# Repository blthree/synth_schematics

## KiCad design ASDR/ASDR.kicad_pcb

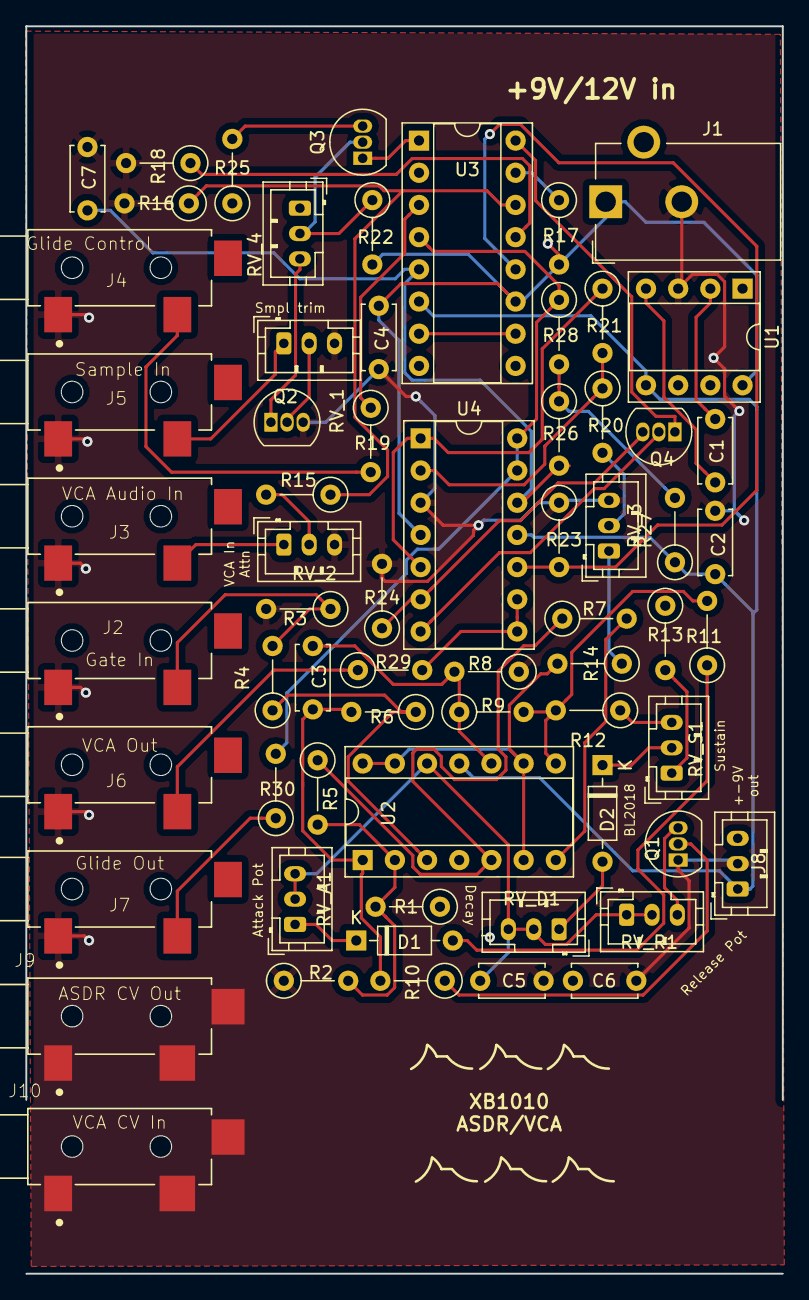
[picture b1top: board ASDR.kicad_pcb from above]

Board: 2 copper layers, 59.7 x 98.4 mm, 65 parts (0 on the bottom side), 52 nets.

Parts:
C1, C2, C5: 10uF; C_Disc_D5.0mm_W2.5mm_P5.00mm
C3: 10nF; C_Disc_D5.0mm_W2.5mm_P5.00mm
C4, C6: 100nF; C_Disc_D5.0mm_W2.5mm_P5.00mm
C7: 1uF; C_Disc_D5.0mm_W2.5mm_P5.00mm
D1, D2: D; D_DO-35_SOD27_P7.62mm_Horizontal
J1: Jack-DC; BarrelJack_CUI_PJ-102AH_Horizontal
J2: Gate In; CUI_SJ2-3592B-SMT-TR
J3: VCA Audio In; CUI_SJ2-3592B-SMT-TR
J4: Glide Control; CUI_SJ2-3592B-SMT-TR
J5: Sample In; CUI_SJ2-3592B-SMT-TR
J6: VCA Out; CUI_SJ2-3592B-SMT-TR
J7: Glide Out; CUI_SJ2-3592B-SMT-TR
J8: Power Out; JST_PH_B3B-PH-K_1x03_P2.00mm_Vertical
J9: ASDR CV Out; CUI_SJ2-3592B-SMT-TR
J10: VCA CV In; CUI_SJ2-3592B-SMT-TR
Q1, Q3, Q4: BC559; TO-92_Inline
Q2: BC548; TO-92_Inline
R1, R10, R20, R21, R22, R25: 33K; R_Axial_DIN0207_L6.3mm_D2.5mm_P5.08mm_Vertical
R2, R4, R11, R14, R16, R18, R29, R30: 1K; R_Axial_DIN0207_L6.3mm_D2.5mm_P5.08mm_Vertical
R3: 22K; R_Axial_DIN0207_L6.3mm_D2.5mm_P5.08mm_Vertical
R5, R12, R13, R15, R17, R23: 10K; R_Axial_DIN0207_L6.3mm_D2.5mm_P5.08mm_Vertical
R6, R7, R8, R9, R26, R27, R28: 1M; R_Axial_DIN0207_L6.3mm_D2.5mm_P5.08mm_Vertical
R19: 100K; R_Axial_DIN0207_L6.3mm_D2.5mm_P5.08mm_Vertical
R24: 5K; R_Axial_DIN0207_L6.3mm_D2.5mm_P5.08mm_Vertical
RV_1, RV_2, RV_3, RV_4: 100K; JST_PH_B3B-PH-K_1x03_P2.00mm_Vertical
RV_A1: 1M; JST_PH_B3B-PH-K_1x03_P2.00mm_Vertical
RV_D1: 1M; JST_PH_B3B-PH-K_1x03_P2.00mm_Vertical
RV_R1: 1M; JST_PH_B3B-PH-K_1x03_P2.00mm_Vertical
RV_S1: 10K; JST_PH_B3B-PH-K_1x03_P2.00mm_Vertical
U1: LTC1044; DIP-8_W7.62mm_Socket
U2, U4: LM324; DIP-14_W7.62mm_Socket
U3: LM13700; DIP-16_W7.62mm_Socket

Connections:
+9V: C4.2, C6.2, J1.1, J8.3, R1.1, R13.1, R17.2, R22.2, R25.1, RV_4.1, U1.8, U2.4, U3.11, U4.4
-9V: C2.2, J8.1, R27.1, U1.5, U2.11, U3.6, U4.11
GND: C2.1, C4.1, C5.2, C6.1, C7.1, J1.2, J2.S, J3.S, J4.S, J5.S, J6.S, J7.S, J8.2, J9.S, J10.S, Q1.1, Q2.3, R2.1, R3.2, R8.1, R16.2, R18.2, R23.1, R24.2, RV_1.3, RV_2.3, RV_3.3, U1.3, U4.3
unnamed: C1.1, U1.2
unnamed: C1.2, U1.4
unnamed: C3.1, R8.2, R9.1, U2.10
unnamed: C3.2, R6.2, R10.2, U2.1
unnamed: C5.1, RV_A1.2, RV_A1.3, RV_D1.2, RV_D1.3, RV_R1.1, RV_R1.2, U2.12
unnamed: C7.2, R26.2, U3.5, U4.12
unnamed: D1.1, RV_A1.1
unnamed: D1.2, R11.1
unnamed: D2.1, RV_S1.2
unnamed: D2.2, RV_D1.1
unnamed: J2.T, R3.1, R4.2
unnamed: J3.T, RV_2.1
unnamed: J4.T, R19.2
unnamed: J5.T, RV_1.1
unnamed: J6.T, R29.1
unnamed: J7.T, R30.1
unnamed: J9.T, R14.1
unnamed: J10.T, RV_3.1
unnamed: Q1.2, R10.1
unnamed: Q1.3, RV_R1.3
unnamed: Q2.1, RV_4.3
unnamed: Q2.2, RV_1.2
unnamed: Q3.1, U3.1
unnamed: Q3.2, R22.1, RV_4.2
unnamed: Q3.3, R25.2
unnamed: Q4.1, U3.16
unnamed: Q4.2, U4.7
unnamed: Q4.3, R24.1, U4.6
unnamed: R1.2, R2.2, R5.2, U2.2
unnamed: R4.1, R6.1, U2.3
unnamed: R5.1, R7.1, U2.5
unnamed: R7.2, U2.7
unnamed: R9.2, R11.2, R12.2, U2.8
unnamed: R12.1, RV_S1.3
unnamed: R13.2, RV_S1.1
unnamed: R14.2, U2.6, U2.9, U2.13, U2.14
unnamed: R15.1, R16.1, U3.14
unnamed: R15.2, RV_2.2
unnamed: R17.1, U3.15
unnamed: R18.1, U3.13
unnamed: R19.1, U3.3
unnamed: R20.1, R21.2, U4.2
unnamed: R20.2, RV_3.2
unnamed: R21.1, U4.1, U4.5
unnamed: R23.2, U3.12, U4.10
unnamed: R26.1, R27.2, R28.2
unnamed: R28.1, R30.2, U3.4, U4.13, U4.14
unnamed: R29.2, U4.8, U4.9
unnamed: U3.7, U3.10

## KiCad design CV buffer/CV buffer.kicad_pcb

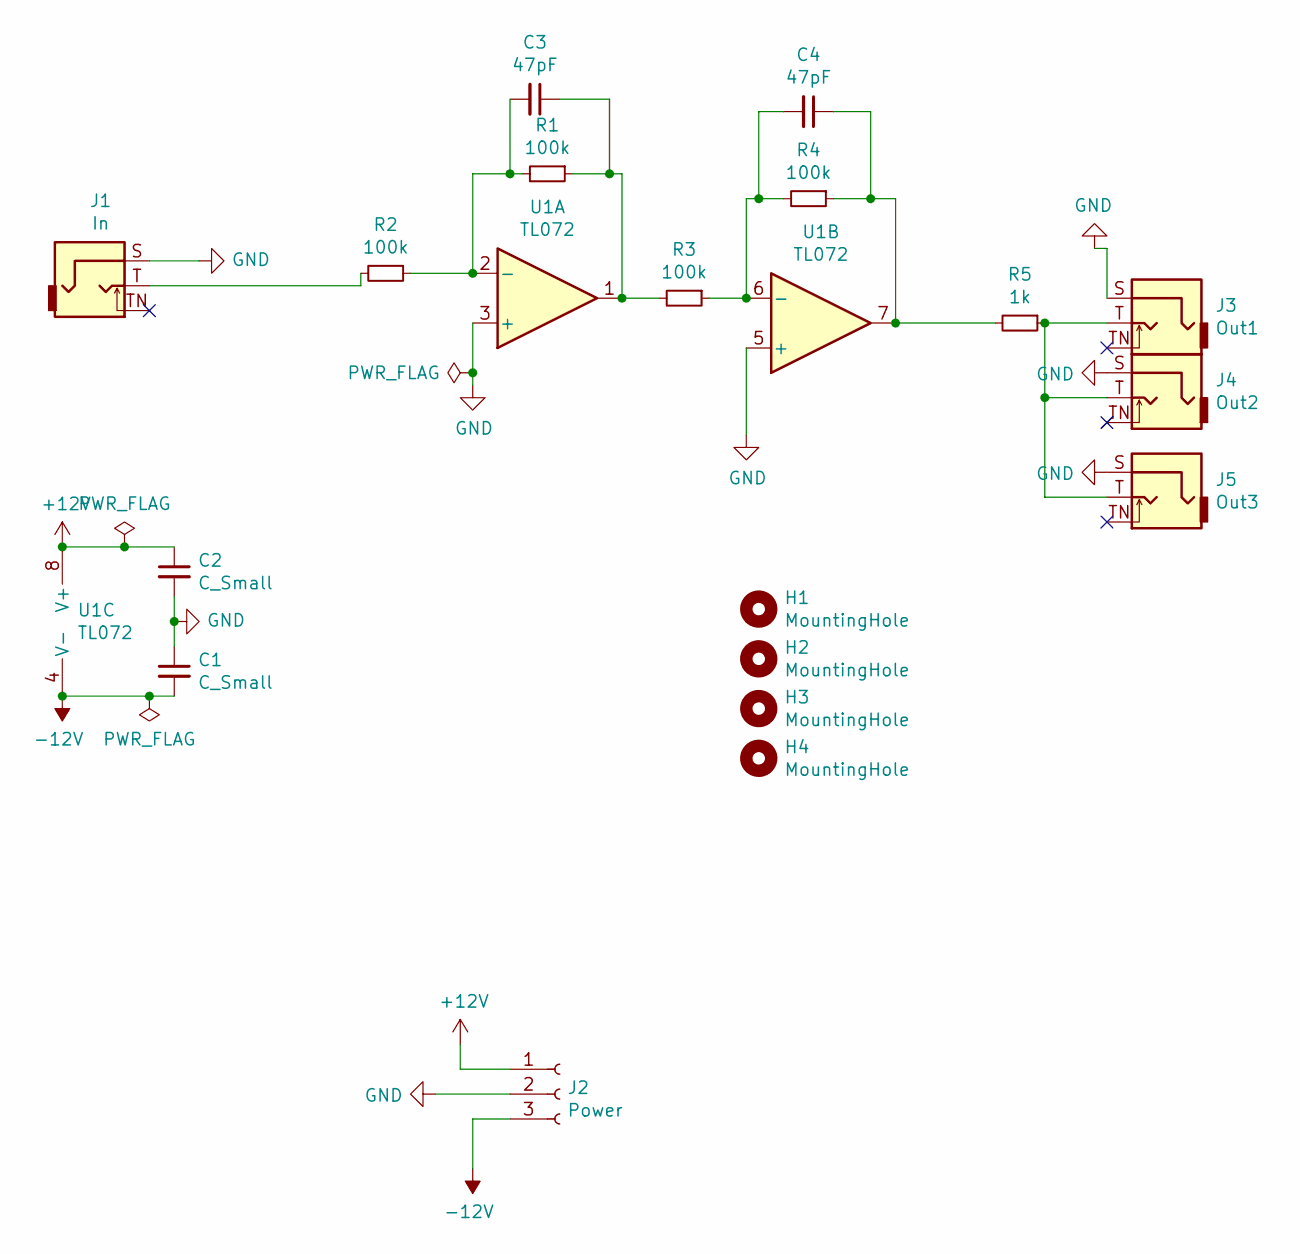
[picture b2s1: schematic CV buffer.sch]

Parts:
C1, C2: C_Small; C_Disc_D4.7mm_W2.5mm_P5.00mm
C3, C4: 47pF; C_Disc_D4.7mm_W2.5mm_P5.00mm
H1, H2, H3, H4: MountingHole; MountingHole_2.7mm_M2.5_ISO14580
J1: In; CUI_SJ2-3592B-SMT-TR
J2: Power; JST_PH_B3B-PH-K_1x03_P2.00mm_Vertical
J3: Out1; CUI_SJ2-3592B-SMT-TR
J4: Out2; CUI_SJ2-3592B-SMT-TR
J5: Out3; CUI_SJ2-3592B-SMT-TR
R1, R2, R3, R4: 100k; R_Axial_DIN0207_L6.3mm_D2.5mm_P5.08mm_Vertical
R5: 1k; R_Axial_DIN0207_L6.3mm_D2.5mm_P5.08mm_Vertical
U1: TL072; DIP-8_W7.62mm_Socket

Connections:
+12V: C2.1, J2.1, U1.8 (V+)
-12V: C1.2, J2.3, U1.4 (V-)
GND: C1.1, C2.2, J1.S, J2.2, J3.S, J4.S, J5.S, U1.3 (+), U1.5 (+)
unnamed: C3.1, R1.1, R3.2, U1.1
unnamed: C3.2, R1.2, R2.1, U1.2 (-)
unnamed: C4.1, R4.1, R5.2, U1.7
unnamed: C4.2, R3.1, R4.2, U1.6 (-)
unnamed: J1.T, R2.2
unnamed: J3.T, J4.T, J5.T, R5.1

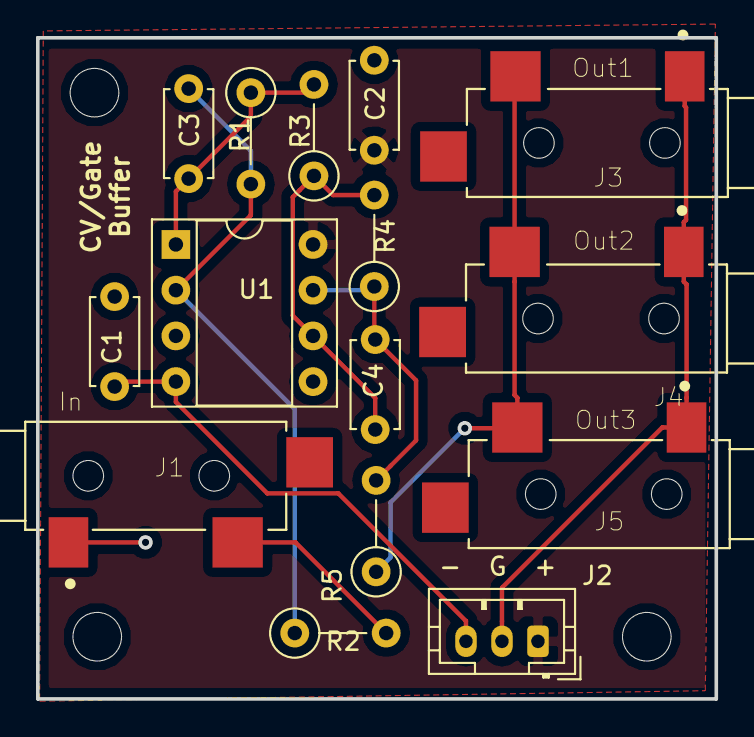
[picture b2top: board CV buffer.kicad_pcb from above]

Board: 2 copper layers, 37.7 x 36.7 mm, 18 parts (0 on the bottom side), 9 nets.

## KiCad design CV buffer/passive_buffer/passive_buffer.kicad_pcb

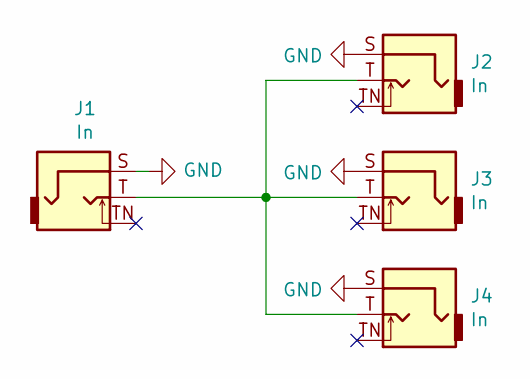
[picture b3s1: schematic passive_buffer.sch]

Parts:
J1, J2, J3, J4: In; CUI_SJ2-3592B-SMT-TR

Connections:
GND: J1.S, J2.S, J3.S, J4.S
unnamed: J1.T, J2.T, J3.T, J4.T

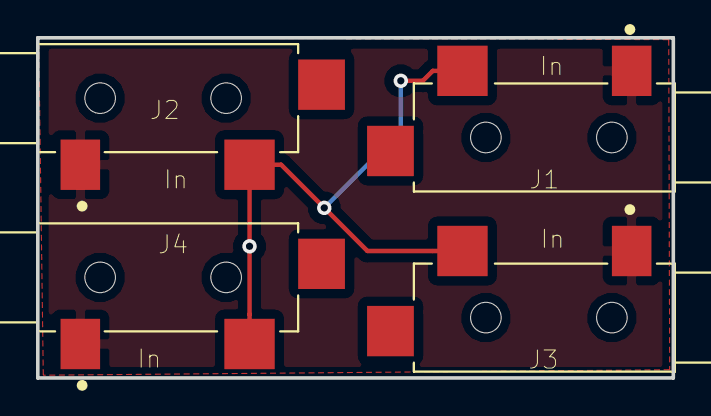
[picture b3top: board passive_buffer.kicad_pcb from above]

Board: 2 copper layers, 35.3 x 18.9 mm, 4 parts (0 on the bottom side), 2 nets.

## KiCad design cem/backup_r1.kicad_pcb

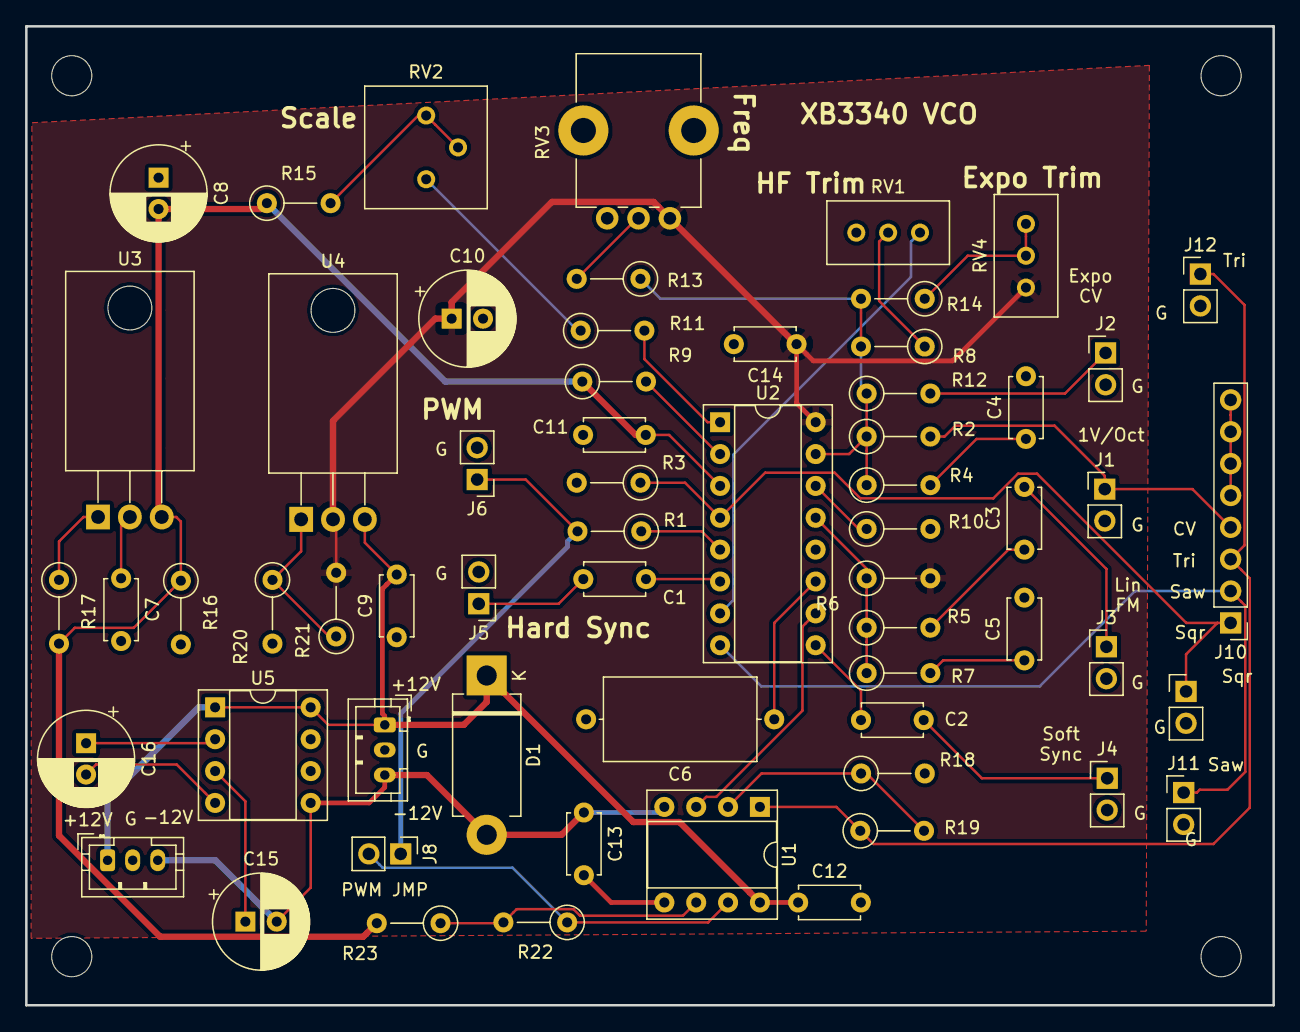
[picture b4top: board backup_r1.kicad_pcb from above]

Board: 2 copper layers, 99.4 x 78.0 mm, 66 parts (0 on the bottom side), 40 nets.

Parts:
C1, C2: 1n; C_Disc_D4.7mm_W2.5mm_P5.00mm
C3, C7, C9, C11, C12, C13, C14: 100n; C_Disc_D4.7mm_W2.5mm_P5.00mm
C4, C5: 10n; C_Disc_D4.7mm_W2.5mm_P5.00mm
C6: 1000p / Mica; C_Axial_L12.0mm_D6.5mm_P15.00mm_Horizontal
C8, C10: 10uF; CP_Radial_D7.5mm_P2.50mm
C15, C16: 100uF; CP_Radial_D7.5mm_P2.50mm
D1: D_ALT; D_DO-201AD_P12.70mm_Horizontal
H1, H2, H3, H4: MountingHole; MountingHole_3.2mm_M3_ISO7380
J1: 1V/Oct; PinHeader_1x02_P2.54mm_Vertical
J2: Expo CV; PinHeader_1x02_P2.54mm_Vertical
J3: Linear FM; PinHeader_1x02_P2.54mm_Vertical
J4: Soft Sync; PinHeader_1x02_P2.54mm_Vertical
J5: Hard Sync; PinHeader_1x02_P2.54mm_Vertical
J6, J11, J12, J13: PWM; PinHeader_1x02_P2.54mm_Vertical
J7, J9: Power; JST_PH_B3B-PH-K_1x03_P2.00mm_Vertical
J8: Sqr Jump; PinHeader_1x02_P2.54mm_Vertical
J10: Conn_01x08_Female; PinHeader_1x08_P2.54mm_Vertical
R1, R22: 10k; R_Axial_DIN0207_L6.3mm_D2.5mm_P5.08mm_Vertical
R2, R12, R13: 100k; R_Axial_DIN0207_L6.3mm_D2.5mm_P5.08mm_Vertical
R3: 51K; R_Axial_DIN0207_L6.3mm_D2.5mm_P5.08mm_Vertical
R4, R7: 470; R_Axial_DIN0207_L6.3mm_D2.5mm_P5.08mm_Vertical
R5, R6: 1M; R_Axial_DIN0207_L6.3mm_D2.5mm_P5.08mm_Vertical
R8: 560k; R_Axial_DIN0207_L6.3mm_D2.5mm_P5.08mm_Vertical
R9, R15: 5.6k; R_Axial_DIN0207_L6.3mm_D2.5mm_P5.08mm_Vertical
R10: 1.8k; R_Axial_DIN0207_L6.3mm_D2.5mm_P5.08mm_Vertical
R11: 18K; R_Axial_DIN0207_L6.3mm_D2.5mm_P5.08mm_Vertical
R14: 220K; R_Axial_DIN0207_L6.3mm_D2.5mm_P5.08mm_Vertical
R16: 680R; R_Axial_DIN0207_L6.3mm_D2.5mm_P5.08mm_Vertical
R17, R21: 220R; R_Axial_DIN0207_L6.3mm_D2.5mm_P5.08mm_Vertical
R18, R19: 10K; R_Axial_DIN0207_L6.3mm_D2.5mm_P5.08mm_Vertical
R20: 2K; R_Axial_DIN0207_L6.3mm_D2.5mm_P5.08mm_Vertical
R23: 20k; R_Axial_DIN0207_L6.3mm_D2.5mm_P5.08mm_Vertical
RV1: 10k; Potentiometer_Bourns_3296W_Vertical
RV2: 5K; Potentiometer_Bourns_3386P_Vertical
RV3: 100k; Potentiometer_Bourns_PTV09A-1_Single_Vertical
RV4: R_POT_TRIM; Potentiometer_Bourns_3296W_Vertical
U1: TL072; DIP-8_W7.62mm_Socket
U2: CEM3340; DIP-16_W7.62mm_Socket
U3: LM337_TO220; TO-220-3_Horizontal_TabDown
U4: LM317_3PinPackage; TO-220-3_Horizontal_TabDown
U5: LTC1044; DIP-8_W7.62mm_Socket

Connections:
1V-Oct: J1.1, J10.4, R2.2
+2.5V: J8.2, R22.1, U1.7
+10V: C10.1, C14.1, R6.2, R21.2, RV3.1, RV4.3, U2.16, U4.2
+12V: C9.2, C12.1, D1.1, J7.1, J9.1, U1.8, U4.3, U5.1, U5.8
-5V: C8.2, C11.2, R9.1, R15.1, R16.1, R17.2, R23.2, U2.3, U3.3
-12V: C7.1, C13.1, C15.2, D1.2, J7.3, J9.3, U1.4, U3.2, U5.5
ExpoCV: J2.1, R12.2
GND: C4.2, C5.2, C6.2, C7.2, C8.1, C9.1, C10.2, C11.1, C12.2, C13.2, C14.2, C15.1, J1.2, J2.2, J3.2, J4.2, J5.2, J6.2, J7.2, J9.2, J10.5, J10.6, J10.7, J10.8, J11.2, J12.2, J13.2, R3.2, R10.2, R16.2, R18.2, R20.2, RV1.3, RV3.3, U1.5, U2.12, U5.3
unnamed: C1.1, U2.6
unnamed: C1.2, J5.1
unnamed: C2.1, U2.9
unnamed: C2.2, J4.1
unnamed: C3.1, R5.2
unnamed: C3.2, J3.1
unnamed: C4.1, R4.2
unnamed: C5.1, R7.2
unnamed: C6.1, U2.11
unnamed: C16.1, U5.2
unnamed: C16.2, U5.4
unnamed: R1.1, U2.5
unnamed: R5.1, R6.1, R7.1, U2.13
unnamed: R8.1, RV1.2
unnamed: R9.2, U2.2
unnamed: R10.1, U2.14
unnamed: R11.1, RV2.1
unnamed: R11.2, U2.1
unnamed: R2.1, R4.1, R8.2, R12.1, R13.1, R14.2, U2.15
unnamed: R13.2, RV3.2
unnamed: R14.1, RV4.1, RV4.2
unnamed: R15.2, RV2.2, RV2.3
unnamed: R17.1, U3.1
unnamed: R18.1, R19.2, U1.2
unnamed: R20.1, R21.1, U4.1
unnamed: R22.2, R23.1, U1.6
unnamed: RV1.1, U2.7
unnamed: U1.3, U2.10
PWM_CV: J6.1, J8.1, R1.2
Saw: J10.2, J11.1, U2.8
Sqr: J10.1, J13.1, R3.1, U2.4
Tri: J10.3, J12.1, R19.1, U1.1

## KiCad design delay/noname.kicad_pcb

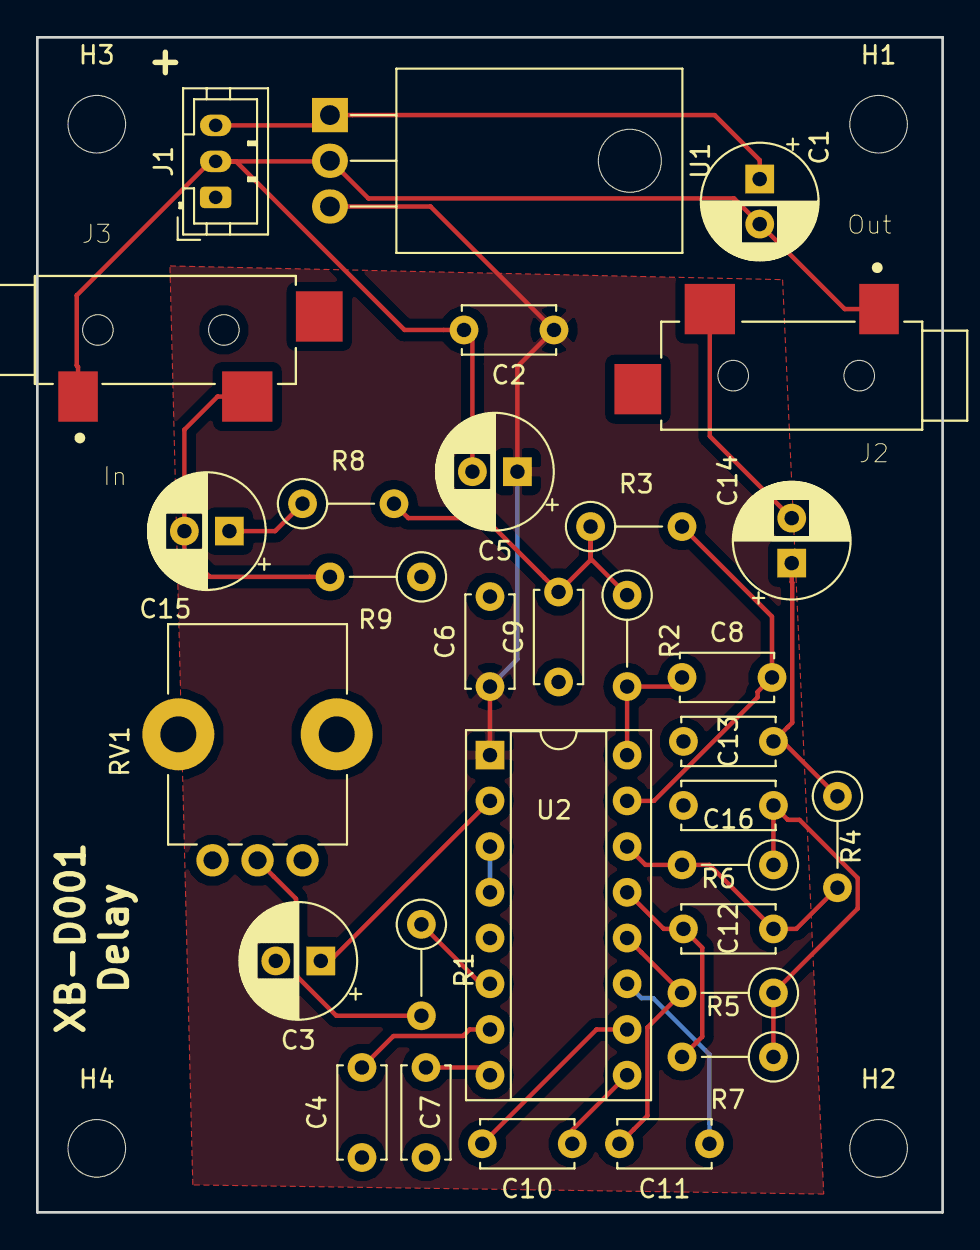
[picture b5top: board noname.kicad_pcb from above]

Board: 2 copper layers, 50.3 x 65.3 mm, 35 parts (0 on the bottom side), 22 nets.

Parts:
C1: CP; CP_Radial_D6.3mm_P2.50mm
C2: C; C_Disc_D5.0mm_W2.5mm_P5.00mm
C3: 47uF; CP_Radial_D6.3mm_P2.50mm
C4, C6, C7, C10, C11, C13: 0.1uF; C_Disc_D5.0mm_W2.5mm_P5.00mm
C5: 100uF; CP_Radial_D6.3mm_P2.50mm
C8, C12: 560pF; C_Disc_D5.0mm_W2.5mm_P5.00mm
C9, C16: 5600pF; C_Disc_D5.0mm_W2.5mm_P5.00mm
C14: 10uF; CP_Radial_D6.3mm_P2.50mm
C15: 4.7uF; CP_Radial_D6.3mm_P2.50mm
H1, H2, H3, H4: MountingHole; MountingHole_3.2mm_M3_ISO7380
J1: Conn_01x03_Female; JST_PH_B3B-PH-K_1x03_P2.00mm_Vertical
J2: Out; CUI_SJ2-3592B-SMT-TR
J3: In; CUI_SJ2-3592B-SMT-TR
R1: 1k; R_Axial_DIN0207_L6.3mm_D2.5mm_P5.08mm_Vertical
R2, R7: 10k; R_Axial_DIN0207_L6.3mm_D2.5mm_P5.08mm_Vertical
R3, R5, R6, R8: 15k; R_Axial_DIN0207_L6.3mm_D2.5mm_P5.08mm_Vertical
R4: 2.74k; R_Axial_DIN0207_L6.3mm_D2.5mm_P5.08mm_Vertical
R9: 100k; R_Axial_DIN0207_L6.3mm_D2.5mm_P5.08mm_Vertical
RV1: R_POT; Potentiometer_Bourns_PTV09A-1_Single_Vertical
U1: LM7805_TO220; TO-220-3_Horizontal_TabDown
U2: PT2399; DIP-16_W7.62mm_Socket

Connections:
+5V: C2.1, C5.1, C6.1, U1.3, U2.1
+12V: C1.1, J1.3, U1.1
GND: C1.2, C2.2, C3.2, C4.1, C5.2, C6.2, C7.1, C9.1, C13.2, C16.2, J1.2, J2.S, J3.S, R9.1, RV1.1, U1.2, U2.3, U2.4
Input: C15.2, J3.T, R9.2
unnamed: C3.1, U2.2
unnamed: C4.2, U2.7
unnamed: C7.2, U2.8
unnamed: C8.1, R2.2, U2.16
unnamed: C8.2, R3.2, U2.15
unnamed: C9.2, R2.1, R3.1, R8.2
unnamed: C10.1, U2.9
unnamed: C10.2, U2.10
unnamed: C11.1, U2.11
unnamed: C11.2, R5.2, U2.12
unnamed: C12.1, R4.2, R6.2, U2.14
unnamed: C12.2, R7.2, U2.13
unnamed: C13.1, C14.1, R4.1
unnamed: C15.1, R8.1
unnamed: C16.1, R5.1, R6.1, R7.1
unnamed: R1.1, U2.6
unnamed: R1.2, RV1.2
Output: C14.2, J2.T
